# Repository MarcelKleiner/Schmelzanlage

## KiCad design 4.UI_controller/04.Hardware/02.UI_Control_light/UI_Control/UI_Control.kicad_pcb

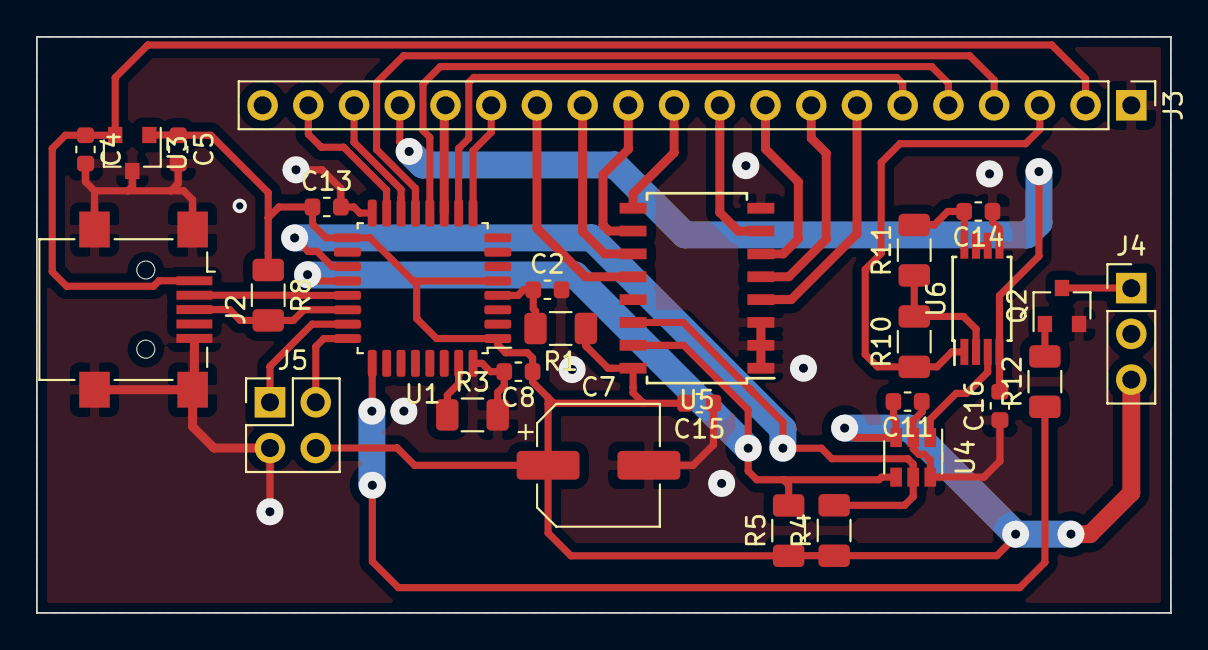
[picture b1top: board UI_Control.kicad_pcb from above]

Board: 2 copper layers, 63.0 x 32.0 mm, 28 parts (0 on the bottom side), 35 nets.

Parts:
C2, C8, C11, C13, C14, C15, C16: 100n; C_0603_1608Metric
C4, C5: C; C_0603_1608Metric
C7: CP; CP_Elec_6.3x5.9
J2: USB_B_Mini; USB_Mini-B_Lumberg_2486_01_Horizontal
J3: LCD; PinHeader_1x20_P2.54mm_Vertical
J4: Conn_01x03_Male; PinHeader_1x03_P2.54mm_Vertical
J5: SWD; PinHeader_2x02_P2.54mm_Vertical
Q2: DMN6140L; SOT-23
R1, R3: 100k; R_1206_3216Metric
R4, R5: 4.7k; R_1206_3216Metric
R8: 1k; R_1206_3216Metric
R10: 6.8k; R_1206_3216Metric
R11: 1.2k; R_1206_3216Metric
R12: 100; R_1206_3216Metric
U1: STM32L412K8Tx; LQFP-32_7x7mm_P0.8mm
U3: MCP1812BT_033TT; SOT-23
U4: MCP4725A; SOT-23-6
U5: TCA9534; SOIC-16W_5.3x10.2mm_P1.27mm
U6: OPA2990; TSSOP-8_4.4x3mm_P0.65mm

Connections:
+3V3: C5.1, C7.1, C8.1, C11.2, C13.1, C15.2, J4.3, J5.4, R1.1, R4.1, R5.1, R8.1, U1.1, U1.5, U1.17, U3.1, U4.3, U5.16
+5V: C14.2, R11.2, U6.8
+5VA: C4.1, J2.1, J3.2, U3.2
/BACKLIGHT: R12.1, U1.25
/CD: J3.4, U1.13
/CE: J3.15, U1.9
/DB0: J3.7, U5.4
/DB1: J3.8, U5.5
/DB2: J3.9, U5.6
/DB3: J3.10, U5.7
/DB4: J3.11, U5.9
/DB5: J3.12, U5.10
/DB6: J3.13, U5.11
/DB7: J3.14, U5.12
/FS: J3.19, U1.15
/MD2: J3.18, U1.14
/RD: J3.5, U1.12
/RESET: J3.16, U1.11
/SCL: R4.2, U1.19, U4.5, U5.14
/SDA: R5.2, U1.20, U4.4, U5.15
/SWCLK: J5.2, U1.24
/SWDIO: J5.1, U1.23
/USB_D+: J2.3, R8.2, U1.22
/USB_D-: J2.2, U1.21
/V0: J3.3, R10.1, U6.1
/VEE: C16.2, J3.17, U6.4
/WR: J3.6, U1.10
GND: C2.2, C4.2, C5.2, C7.2, C8.2, C11.1, C13.2, C14.1, C15.1, C16.1, J2.5, J2.6, J3.1, J5.3, Q2.2, R3.2, U1.16, U1.32, U3.3, U4.2, U4.6, U5.1, U5.2, U5.3, U5.8, U6.5
unnamed: C2.1, R1.2, U1.4
unnamed: J4.1, Q2.3
unnamed: Q2.1, R12.2
unnamed: R3.1, U1.31
unnamed: R10.2, R11.1, U6.2
unnamed: U4.1, U6.3
unnamed: U6.6, U6.7

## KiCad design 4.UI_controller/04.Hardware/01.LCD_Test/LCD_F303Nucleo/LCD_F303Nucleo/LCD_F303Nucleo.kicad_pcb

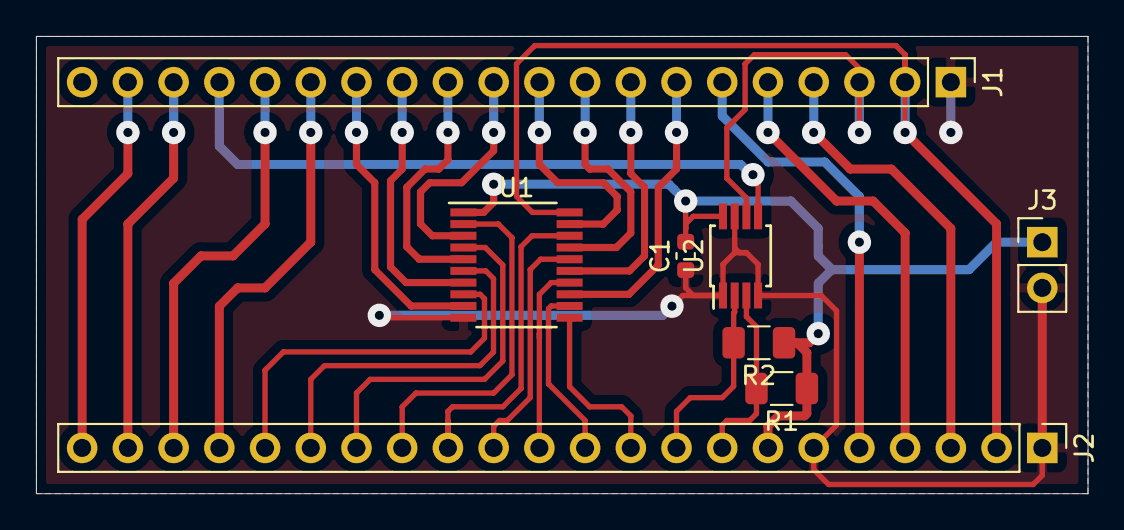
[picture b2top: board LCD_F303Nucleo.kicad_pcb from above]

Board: 2 copper layers, 58.4 x 25.4 mm, 8 parts (0 on the bottom side), 31 nets.

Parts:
C1: 100n; C_0603_1608Metric
J1: Conn_01x20; PinHeader_1x20_P2.54mm_Vertical
J2: Conn_01x22; PinHeader_1x22_P2.54mm_Vertical
J3: Conn_01x02; PinHeader_1x02_P2.54mm_Vertical
R1, R2: 4.7k; R_1206_3216Metric
U1: ST2378ETTR; TSSOP-20_4.4x6.5mm_P0.65mm
U2: MCP4541T; MSOP-8_3x3mm_P0.65mm

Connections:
+3V3: C1.2, J2.7, J3.1, R1.1, R2.1, U1.1, U2.8
+5V: J1.2, J2.2, U1.20
/CE: J1.15, J2.19
/C_D: J1.4, J2.3
/DB0: J1.7, U1.13
/DB1: J1.8, U1.15
/DB2: J1.9, U1.17
/DB3: J1.10, U1.19
/DB4: J1.11, U1.3
/DB5: J1.12, U1.5
/DB6: J1.13, U1.7
/DB7: J1.14, U1.9
/FS: J1.19, J2.22
/IO_Vl1: J2.18, U1.8
/IO_Vl2: J2.17, U1.6
/IO_Vl3: J2.16, U1.4
/IO_Vl4: J2.15, U1.2
/IO_Vl5: J2.14, U1.18
/IO_Vl6: J2.13, U1.16
/IO_Vl7: J2.12, U1.14
/IO_Vl8: J2.11, U1.12
/MD2: J1.18, J2.21
/OE: J2.10, U1.11
/RD: J1.5, J2.4
/RESET: J1.16, J2.20
/SCL: J2.9, R2.2, U2.2
/SDA: J2.8, R1.2, U2.3
/V0: J1.3, U2.6
/VEE: J1.17, U2.5
/WR: J1.6, J2.5
GND: C1.1, J1.1, J2.1, J2.6, J3.2, U1.10, U2.1, U2.4, U2.7

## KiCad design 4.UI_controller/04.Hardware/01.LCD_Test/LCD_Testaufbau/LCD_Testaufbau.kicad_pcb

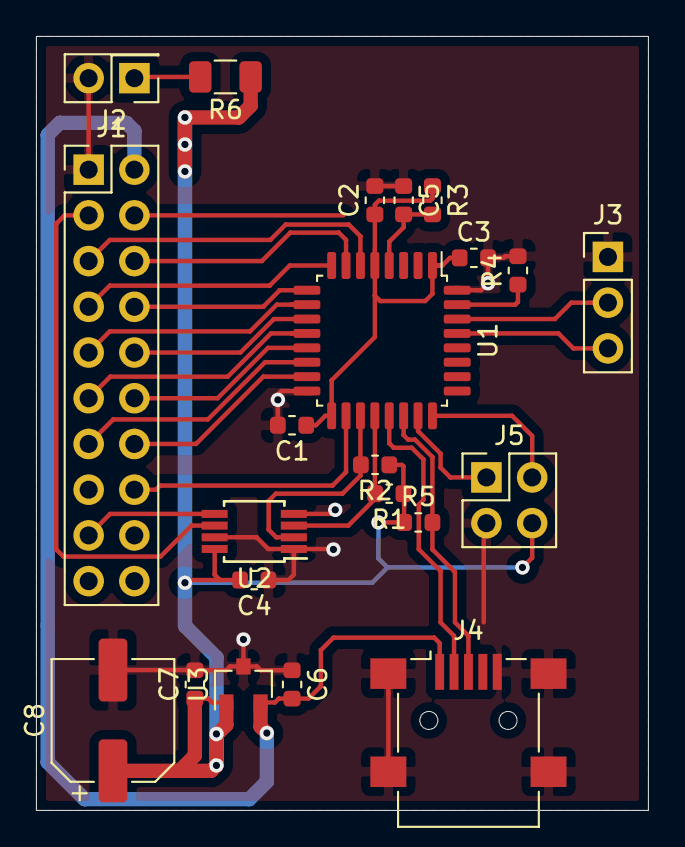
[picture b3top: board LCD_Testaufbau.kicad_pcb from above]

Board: 2 copper layers, 34.0 x 43.0 mm, 22 parts (0 on the bottom side), 28 nets.

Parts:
C1, C2, C3, C4, C5, C6, C7: 100n; C_0603_1608Metric
C8: CP; CP_Elec_6.3x5.9
J1: Conn_02x10_Odd_Even; PinHeader_2x10_P2.54mm_Vertical
J2: Conn_02x01; PinHeader_2x01_P2.54mm_Vertical
J3: Conn_01x03; PinHeader_1x03_P2.54mm_Vertical
J4: USB_B_Mini; USB_Mini-B_Lumberg_2486_01_Horizontal
J5: Conn_02x02_Counter_Clockwise; PinHeader_2x02_P2.54mm_Vertical
R1, R2: 4.7k; R_0603_1608Metric
R3, R4: 100K; R_0603_1608Metric
R5: 1.5K; R_0603_1608Metric
R6: R; R_1206_3216Metric
U1: STM32L412K8Tx; LQFP-32_7x7mm_P0.8mm
U2: MCP4541T; MSOP-8_3x3mm_P0.65mm
U3: MCP1812BT_033TT; SOT-23

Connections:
+3V3: C1.1, C2.1, C3.1, C4.2, C7.1, C8.1, J5.4, R1.1, R2.1, R3.1, R5.1, R6.1, U1.1, U1.5, U1.17, U2.8, U3.1
+5V: C6.2, J1.2, J4.1, U3.2
/C_D: J1.4, U1.3
/DB0: J1.7, U1.8
/DB1: J1.8, U1.9
/DB2: J1.9, U1.10
/DB3: J1.10, U1.11
/DB4: J1.11, U1.12
/DB5: J1.12, U1.13
/DB6: J1.13, U1.14
/DB7: J1.14, U1.15
/RD: J1.5, U1.6
/RESET: J1.16, U1.18
/SCL: R2.2, U1.19, U2.2
/SDA: R1.2, U1.20, U2.3
/SWCLK: J5.2, U1.24
/SWDIO: J5.1, U1.23
/USART_RX: J3.3, U1.29
/USART_TX: J3.2, U1.30
/USB_D+: J4.3, R5.2, U1.22
/USB_D-: J4.2, U1.21
/V0: J1.3, U2.6
/VEE: J1.17, U2.5
/WR: J1.6, U1.7
GND: C1.2, C2.2, C3.2, C4.1, C5.1, C6.1, C7.2, C8.2, J1.1, J2.2, J3.1, J4.5, J4.6, J5.3, R4.2, U1.16, U1.32, U2.1, U2.4, U2.7, U3.3
unnamed: C5.2, R3.2, U1.4
unnamed: J2.1, R6.2
unnamed: R4.1, U1.31

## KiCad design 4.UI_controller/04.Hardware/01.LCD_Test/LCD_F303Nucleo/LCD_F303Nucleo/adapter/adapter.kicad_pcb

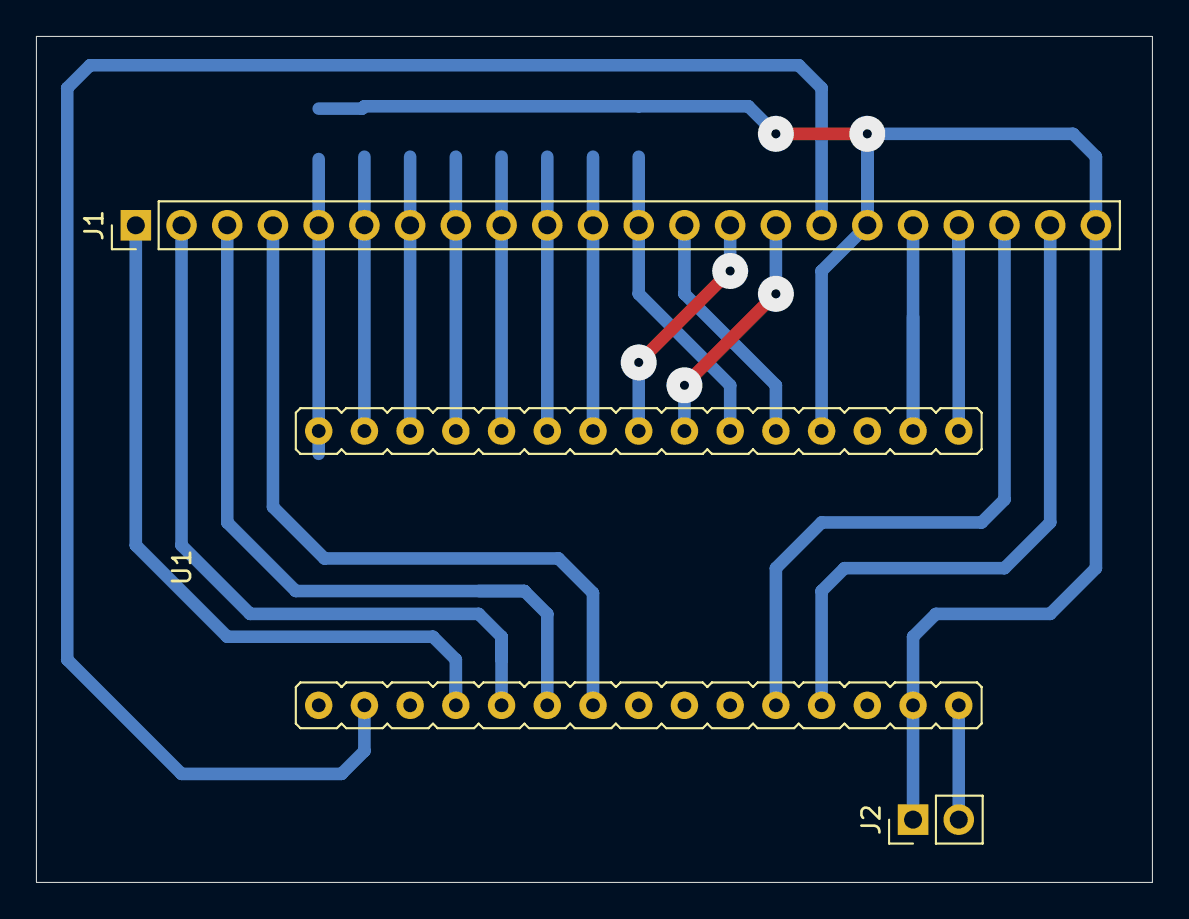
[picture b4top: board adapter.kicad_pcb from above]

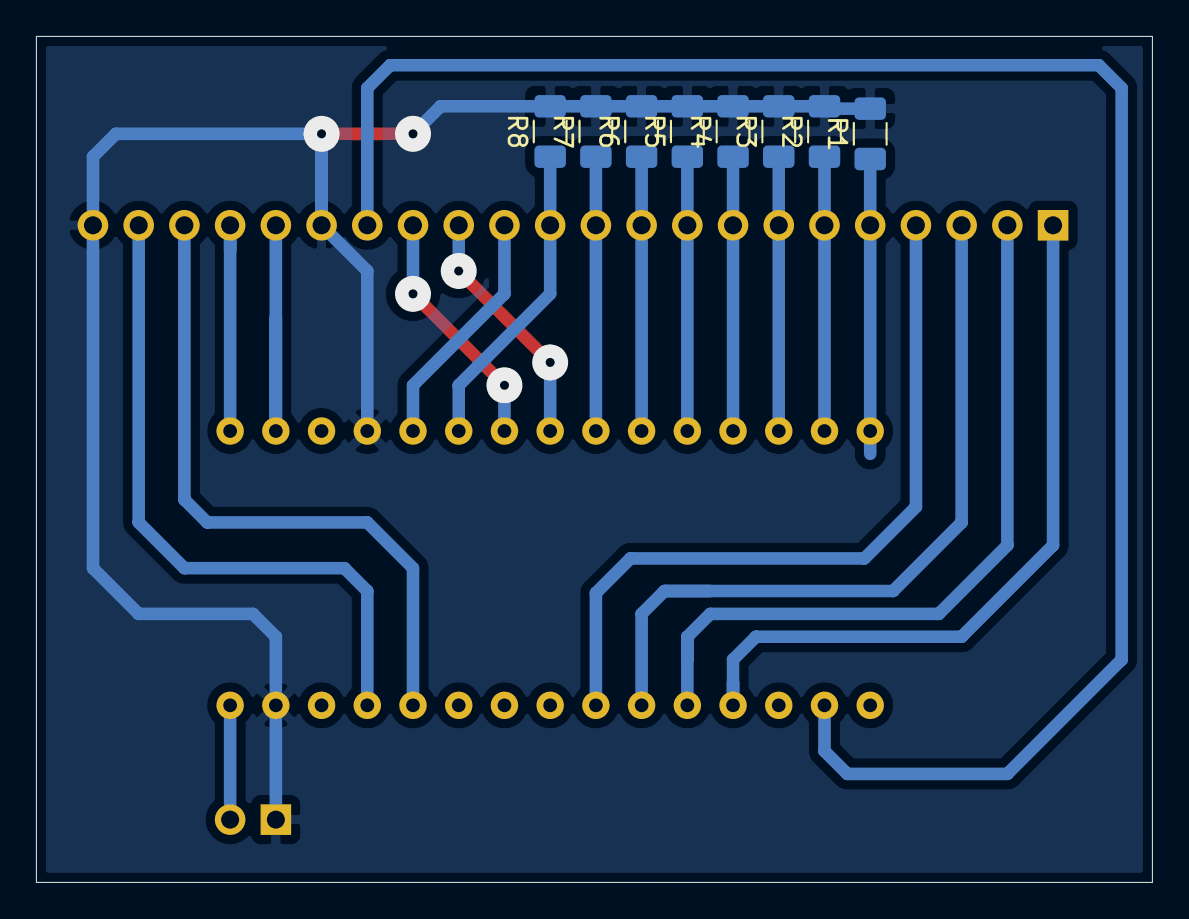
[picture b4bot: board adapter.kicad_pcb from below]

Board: 2 copper layers, 62.0 x 47.0 mm, 11 parts (8 on the bottom side), 22 nets.

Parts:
J1: Conn_01x22_Female; PinHeader_1x22_P2.54mm_Vertical
J2: Conn_01x02_Female; PinHeader_1x02_P2.54mm_Vertical
R1, R2, R3, R4, R5, R6, R7, R8: 1k; R_1206_3216Metric
U1: STM32F303K8T_NUCLEO

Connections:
+3V3: J1.16, U1.14
+5V: J1.21, U1.4
/CD: J1.20, U1.5
/CE: J1.4, U1.9
/DB0: J1.5, R1.1, U1.16
/DB1: J1.6, R2.1, U1.17
/DB2: J1.7, R3.1, U1.18
/DB3: J1.8, R4.1, U1.19
/DB4: J1.9, R5.1, U1.20
/DB5: J1.10, R6.1, U1.21
/DB6: J1.11, R7.1, U1.22
/DB7: J1.12, R8.1, U1.25
/FS: J1.1, U1.12
/MD2: J1.2, U1.11
/OE: J1.13, U1.26
/RD: J1.19, U1.30
/RESET: J1.3, U1.10
/SCL: J1.14, U1.23
/SDA: J1.15, U1.24
/WR: J1.18, U1.29
GND: J1.17, J1.22, J2.1, R1.2, R2.2, R3.2, R4.2, R5.2, R6.2, R7.2, R8.2, U1.2, U1.27
unnamed: J2.2, U1.1

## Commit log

2020-06-07 update UI control Software / add Dokumente DEM24018 T6963C
2020-06-15 update Software LCD Test
2020-06-29 update Layout
2020-07-04 Update Software
2020-07-06 add graphic function
2020-07-08 change graphic algorithm
2020-07-09 update Graphic Test
2020-07-09 update GUI test
